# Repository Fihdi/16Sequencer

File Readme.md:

# 34hp 16 Step Sequencer

A 16-Step sequencer with individual CV knobs and 4 programmable gate outputs, including a probability gate output. Input gates can control the Clock, Reset, Direction and Pause/Play.

To program a gate channel, hold down the channel button (A through D) and select or deselect the steps are active. 

The functionality is similar to the famous "Baby 8" sequencers but instead of a CD4017, a TCA9555 IO-expander sends 5 or 0V to the potentiometers, which are then summed together. Another TCA9555 is used for the LEDs and push-buttons, both of which are set up in a 4x4 Matrix, allowing both of them to be handled by a single expander.

ToDo:

- Individual gate channel lengths: The length of every gate channel should be set individually with the LENGTH knob. Turning the LENGTH knob while holding down a channel button will change the length of that gate channel. Turning the LENGTH knob on its own only changes the length of the CV channel.

- Ratcheting: Pushing on a step button multiple times should allow for re-triggering (2, 4 or 8 times that of the CLK signal)

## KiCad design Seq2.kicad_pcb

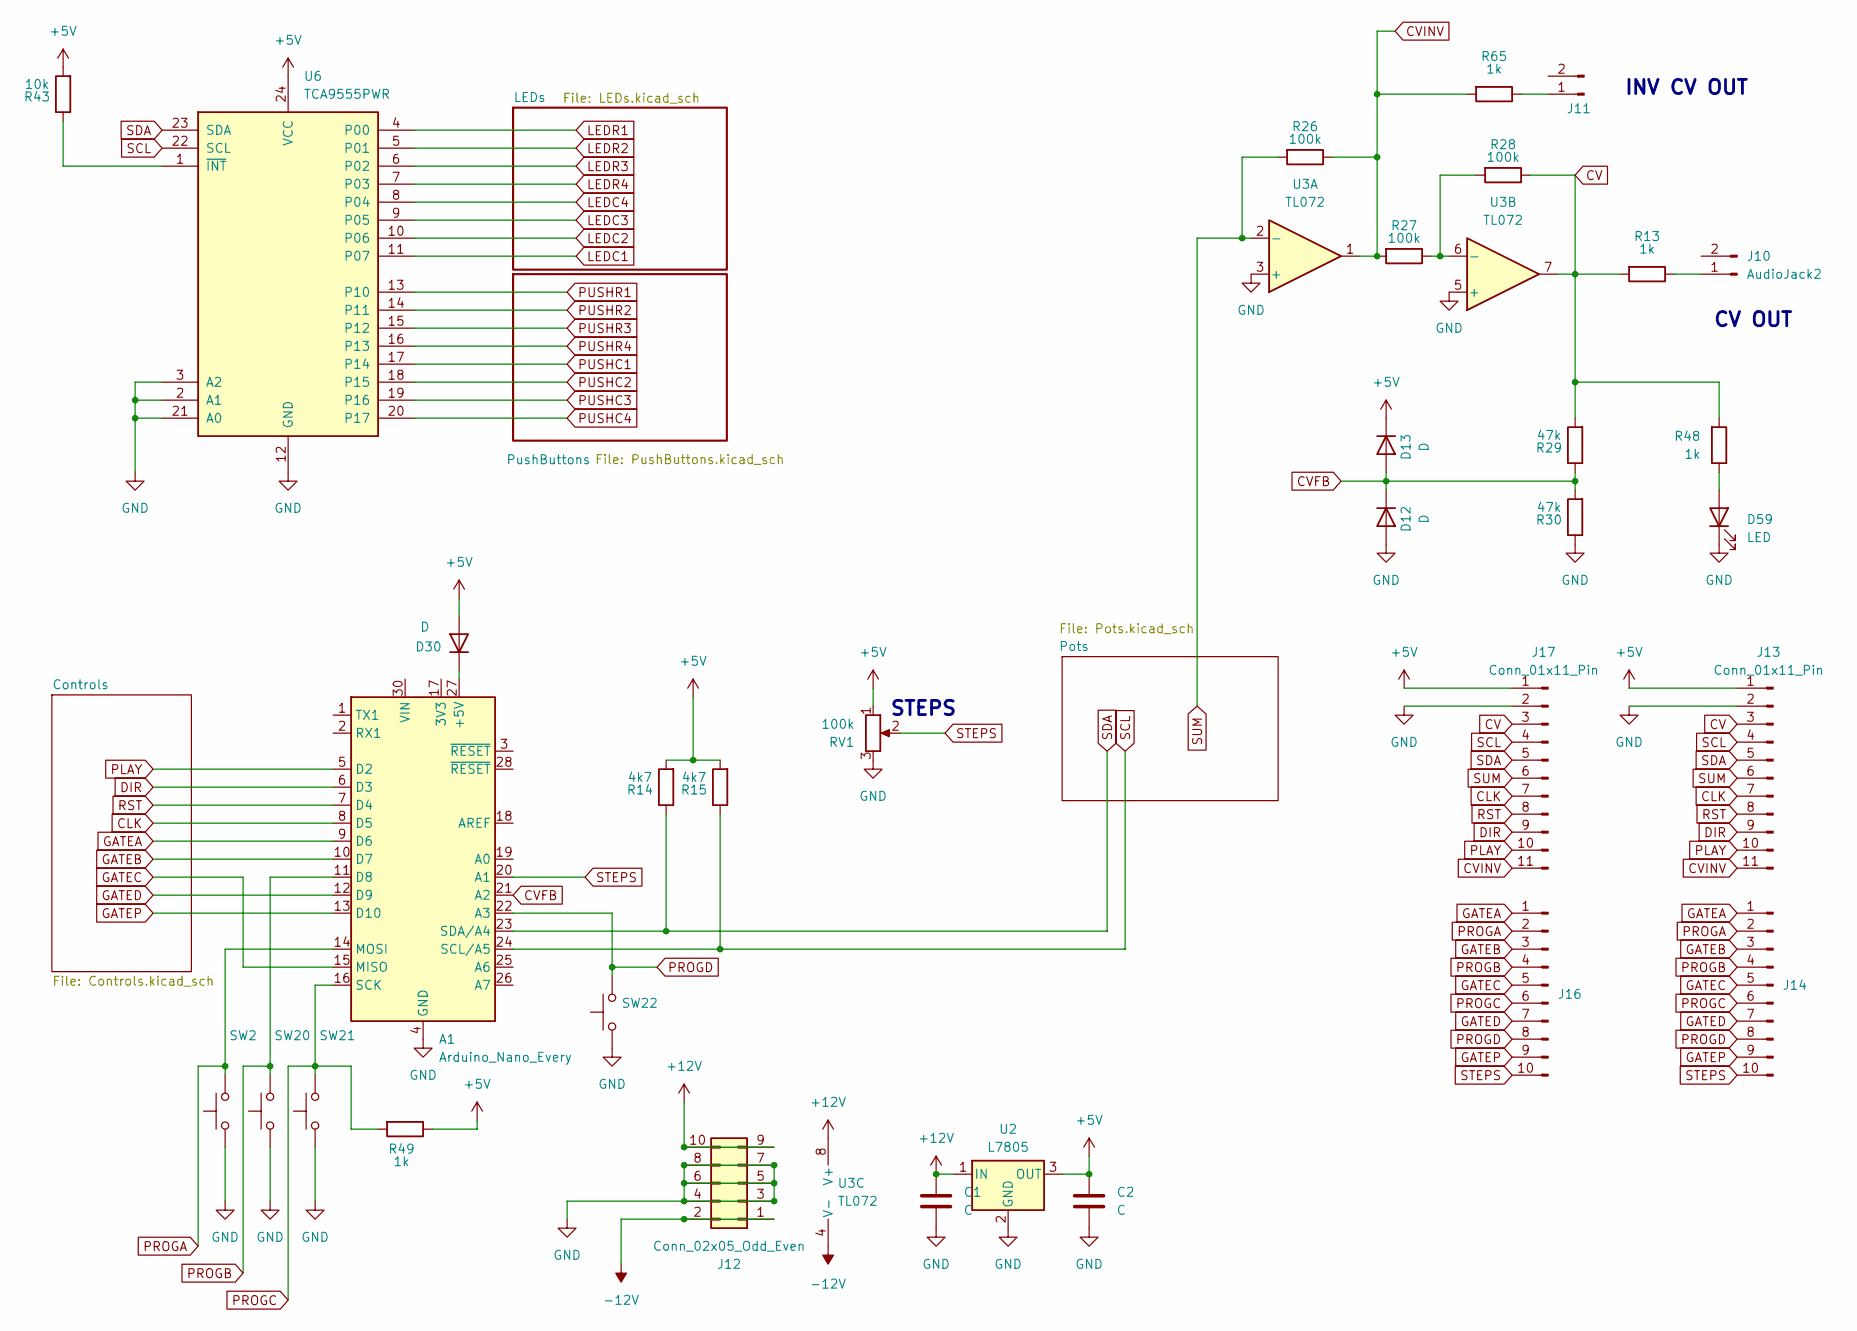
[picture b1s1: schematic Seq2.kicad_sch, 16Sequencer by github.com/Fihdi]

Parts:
A1: Arduino_Nano_Every; Arduino_Nano
C1, C2: C; C_Rect_L7.0mm_W3.5mm_P5.00mm
D12, D13, D30: D; D_1206_3216Metric
D59: LED; LED_D3.0mm
J10, J11: AudioJack2; 3mm5 Mono Aux
J12: Conn_02x05_Odd_Even; PinHeader_2x05_P2.54mm_Vertical
J13, J17: Conn_01x11_Pin; PinHeader_1x11_P2.54mm_Vertical
J14, J16: Conn_01x10_Pin; PinHeader_1x10_P2.54mm_Vertical
R13, R48, R49, R65: 1k; R_1206_3216Metric
R14, R15: 4k7; R_1206_3216Metric
R26, R27, R28: 100k; R_1206_3216Metric
R29, R30: 47k; R_1206_3216Metric
R43: 10k; R_1206_3216Metric
RV1: 100k; Potentiometer_Alpha_RD901F-40-00D_Single_Vertical_CircularH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
SW2, SW20, SW21, SW22: SW_Push; PushButton
U2: L7805; TO-252-3_TabPin2
U3: TL072; DIP-8_W7.62mm
U6: TCA9555PWR; SSOP-24_5.3x8.2mm_P0.65mm

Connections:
+5V: C2.1, D13.1 (K), D30.2 (A), J13.1, J17.1, R14.2, R15.2, R43.2, R49.1, RV1.1, U2.3 (OUT), U6.24 (VCC); also elsewhere on the board
+12V: C1.1, J12.9, J12.10, U2.1 (IN), U3.8 (V+)
-12V: J12.1, J12.2, U3.4 (V-)
CLK: A1.8 (D5), J13.7, J17.7; also elsewhere on the board
CV: J13.3, J17.3, R13.2, R28.1, R29.2, R48.2, U3.7
CVFB: A1.21 (A2), D12.1 (K), D13.2 (A), R29.1, R30.2
CVINV: J13.11, J17.11, R26.1, R27.2, R65.2, U3.1
DIR: A1.6 (D3), J13.9, J17.9; also elsewhere on the board
GATEA: A1.9 (D6), J14.1, J16.1; also elsewhere on the board
GATEB: A1.10 (D7), J14.3, J16.3; also elsewhere on the board
GATEC: A1.15 (MISO), J14.5, J16.5; also elsewhere on the board
GATED: A1.12 (D9), J14.7, J16.7; also elsewhere on the board
GATEP: A1.13 (D10), J14.9, J16.9; also elsewhere on the board
GND: A1.4 (GND), A1.29 (GND), C1.2, C2.2, D12.2 (A), D59.1 (K), J12.3, J12.4, J12.5, J12.6, J12.7, J12.8, J13.2, J17.2, R30.1, RV1.3, SW2.1, SW20.1, SW21.1, SW22.1, U2.2 (GND), U3.3 (+), U3.5 (+), U6.2 (A1), U6.3 (A2), U6.12 (GND), U6.21 (A0); also elsewhere on the board
LEDC1: U6.11 (P07); also elsewhere on the board
LEDC2: U6.10 (P06); also elsewhere on the board
LEDC3: U6.9 (P05); also elsewhere on the board
LEDC4: U6.8 (P04); also elsewhere on the board
LEDR1: U6.4 (P00); also elsewhere on the board
LEDR2: U6.5 (P01); also elsewhere on the board
LEDR3: U6.6 (P02); also elsewhere on the board
LEDR4: U6.7 (P03); also elsewhere on the board
unnamed: A1.27 (+5V), D30.1 (K)
unnamed: D59.2 (A), R48.1
unnamed: J10.1, R13.1
unnamed: J11.1, R65.1
unnamed: R27.1, R28.2, U3.6 (-)
unnamed: R43.1, U6.1 (~INT)
PLAY: A1.5 (D2), J13.10, J17.10; also elsewhere on the board
PROGA: A1.14 (MOSI), J14.2, J16.2, SW2.2
PROGB: A1.11 (D8), J14.4, J16.4, SW20.2
PROGC: A1.16 (SCK), J14.6, J16.6, R49.2, SW21.2
PROGD: A1.22 (A3), J14.8, J16.8, SW22.2
PUSHC1: U6.17 (P14); also elsewhere on the board
PUSHC2: U6.18 (P15); also elsewhere on the board
PUSHC3: U6.19 (P16); also elsewhere on the board
PUSHC4: U6.20 (P17); also elsewhere on the board
PUSHR1: U6.13 (P10); also elsewhere on the board
PUSHR2: U6.14 (P11); also elsewhere on the board
PUSHR3: U6.15 (P12); also elsewhere on the board
PUSHR4: U6.16 (P13); also elsewhere on the board
RST: A1.7 (D4), J13.8, J17.8; also elsewhere on the board
SCL: A1.24 (SCL/A5), J13.4, J17.4, R15.1, U6.22 (SCL); also elsewhere on the board
SDA: A1.23 (SDA/A4), J13.5, J17.5, R14.1, U6.23 (SDA); also elsewhere on the board
STEPS: A1.20 (A1), J14.10, J16.10, RV1.2
SUM: J13.6, J17.6, R26.2, U3.2 (-); also elsewhere on the board

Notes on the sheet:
STEPS
CV OUT
INV CV OUT

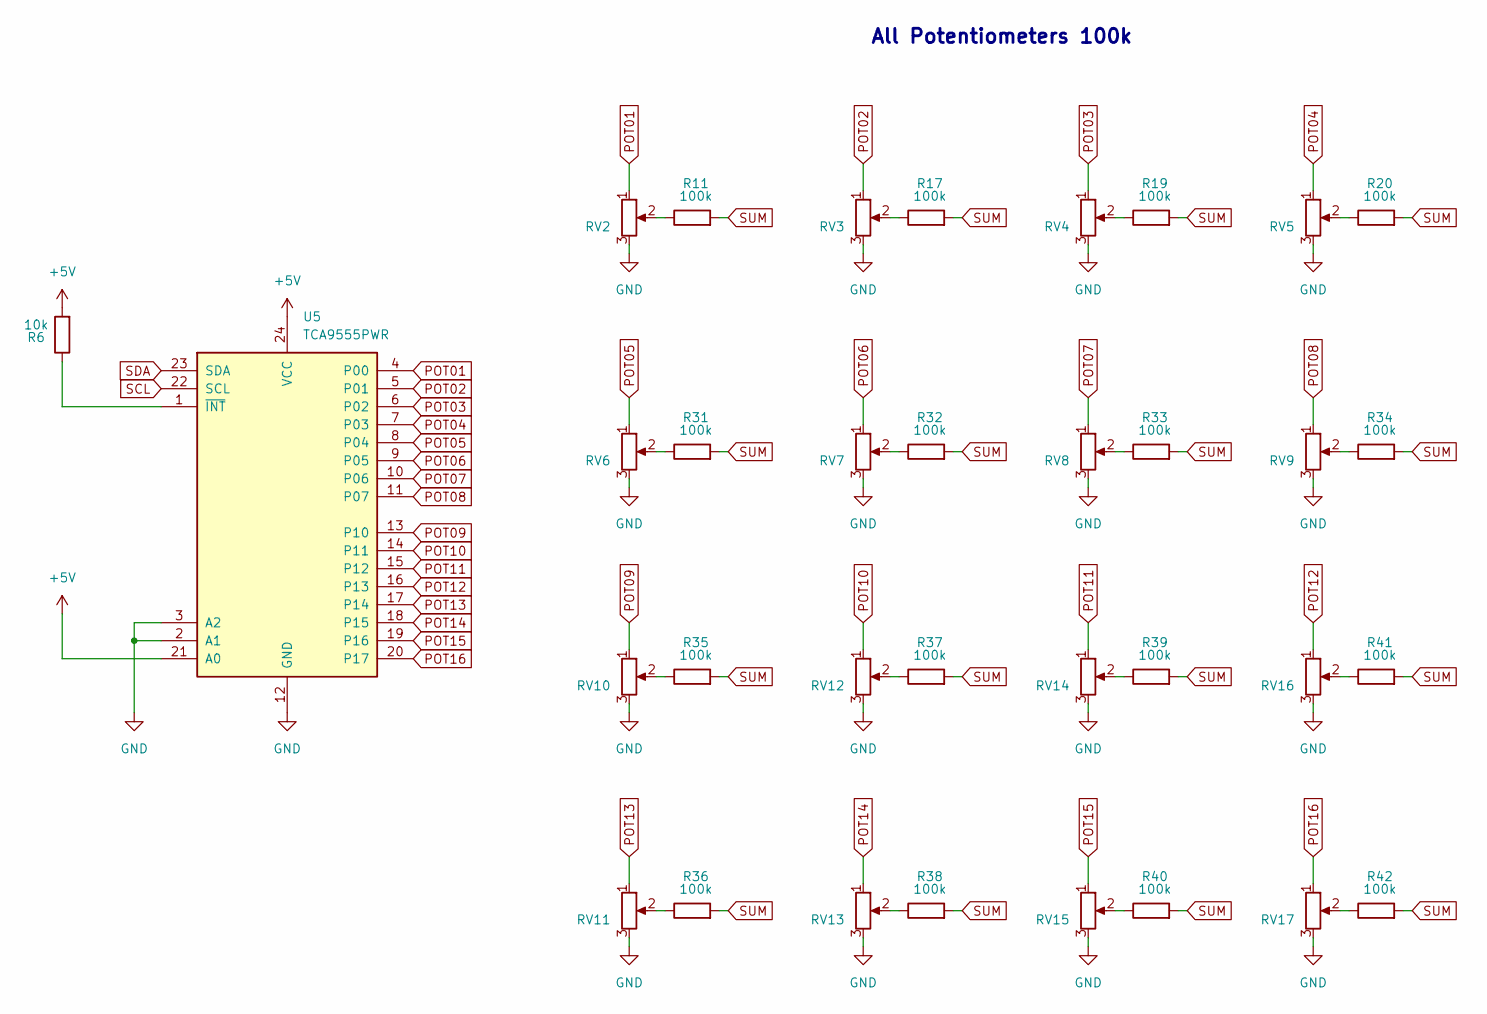
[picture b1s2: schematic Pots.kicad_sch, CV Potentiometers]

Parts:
R6: 10k; R_1206_3216Metric
R11, R17, R19, R20, R31, R32, R33, R34, R35, R36, R37, R38, R39, R40, R41, R42: 100k; R_1206_3216Metric
RV2, RV3, RV4, RV5, RV6, RV9, RV10, RV11, RV12, RV13, RV14, RV15, RV16, RV17: R_Potentiometer; Potentiometer_Alpha_RD901F-40-00D_Single_Vertical_CircularH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
RV7, RV8: R_Potentiometer; Alpha_RD901_NoMountPins
U5: TCA9555PWR; SSOP-24_5.3x8.2mm_P0.65mm

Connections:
+5V: R6.2, U5.21 (A0), U5.24 (VCC); also elsewhere on the board
GND: RV2.3, RV3.3, RV4.3, RV5.3, RV6.3, RV7.3, RV8.3, RV9.3, RV10.3, RV11.3, RV12.3, RV13.3, RV14.3, RV15.3, RV16.3, RV17.3, U5.2 (A1), U5.3 (A2), U5.12 (GND); also elsewhere on the board
unnamed: R11.1, RV2.2
unnamed: R17.1, RV3.2
unnamed: R19.1, RV4.2
unnamed: R20.1, RV5.2
unnamed: R31.1, RV6.2
unnamed: R32.1, RV7.2
unnamed: R33.1, RV8.2
unnamed: R34.1, RV9.2
unnamed: R35.1, RV10.2
unnamed: R36.1, RV11.2
unnamed: R37.1, RV12.2
unnamed: R38.1, RV13.2
unnamed: R39.1, RV14.2
unnamed: R40.1, RV15.2
unnamed: R41.1, RV16.2
unnamed: R42.1, RV17.2
unnamed: R6.1, U5.1 (~INT)
POT01: RV2.1, U5.4 (P00)
POT02: RV3.1, U5.5 (P01)
POT03: RV4.1, U5.6 (P02)
POT04: RV5.1, U5.7 (P03)
POT05: RV6.1, U5.8 (P04)
POT06: RV7.1, U5.9 (P05)
POT07: RV8.1, U5.10 (P06)
POT08: RV9.1, U5.11 (P07)
POT09: RV10.1, U5.13 (P10)
POT10: RV12.1, U5.14 (P11)
POT11: RV14.1, U5.15 (P12)
POT12: RV16.1, U5.16 (P13)
POT13: RV11.1, U5.17 (P14)
POT14: RV13.1, U5.18 (P15)
POT15: RV15.1, U5.19 (P16)
POT16: RV17.1, U5.20 (P17)
SCL: U5.22 (SCL); also elsewhere on the board
SDA: U5.23 (SDA); also elsewhere on the board
SUM: R11.2, R17.2, R19.2, R20.2, R31.2, R32.2, R33.2, R34.2, R35.2, R36.2, R37.2, R38.2, R39.2, R40.2, R41.2, R42.2; also elsewhere on the board

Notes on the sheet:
All Potentiometers 100k

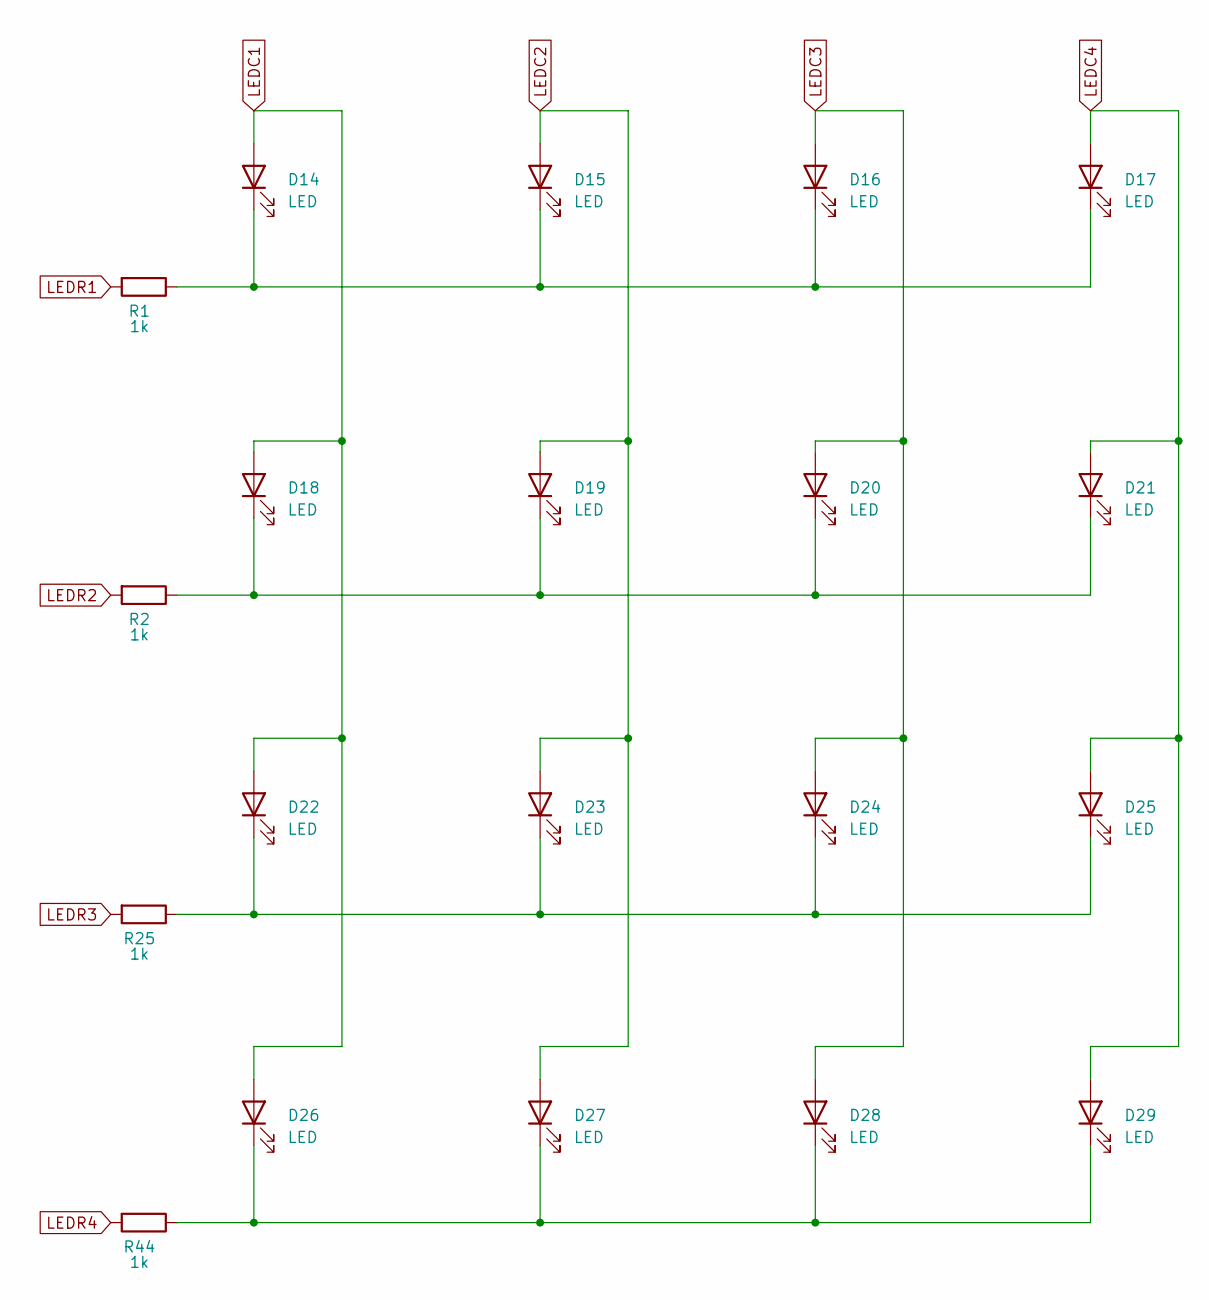
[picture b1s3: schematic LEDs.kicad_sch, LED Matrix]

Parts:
D14, D15, D16, D17, D18, D19, D20, D21, D22, D23, D24, D25, D26, D27, D28, D29: LED; LED_D3.0mm
R1, R2, R25, R44: 1k; R_1206_3216Metric

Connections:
LEDC1: D14.2 (A), D18.2 (A), D22.2 (A), D26.2 (A); also elsewhere on the board
LEDC2: D15.2 (A), D19.2 (A), D23.2 (A), D27.2 (A); also elsewhere on the board
LEDC3: D16.2 (A), D20.2 (A), D24.2 (A), D28.2 (A); also elsewhere on the board
LEDC4: D17.2 (A), D21.2 (A), D25.2 (A), D29.2 (A); also elsewhere on the board
LEDR1: R1.2; also elsewhere on the board
LEDR2: R2.2; also elsewhere on the board
LEDR3: R25.2; also elsewhere on the board
LEDR4: R44.2; also elsewhere on the board
unnamed: D14.1 (K), D15.1 (K), D16.1 (K), D17.1 (K), R1.1
unnamed: D18.1 (K), D19.1 (K), D20.1 (K), D21.1 (K), R2.1
unnamed: D22.1 (K), D23.1 (K), D24.1 (K), D25.1 (K), R25.1
unnamed: D26.1 (K), D27.1 (K), D28.1 (K), D29.1 (K), R44.1

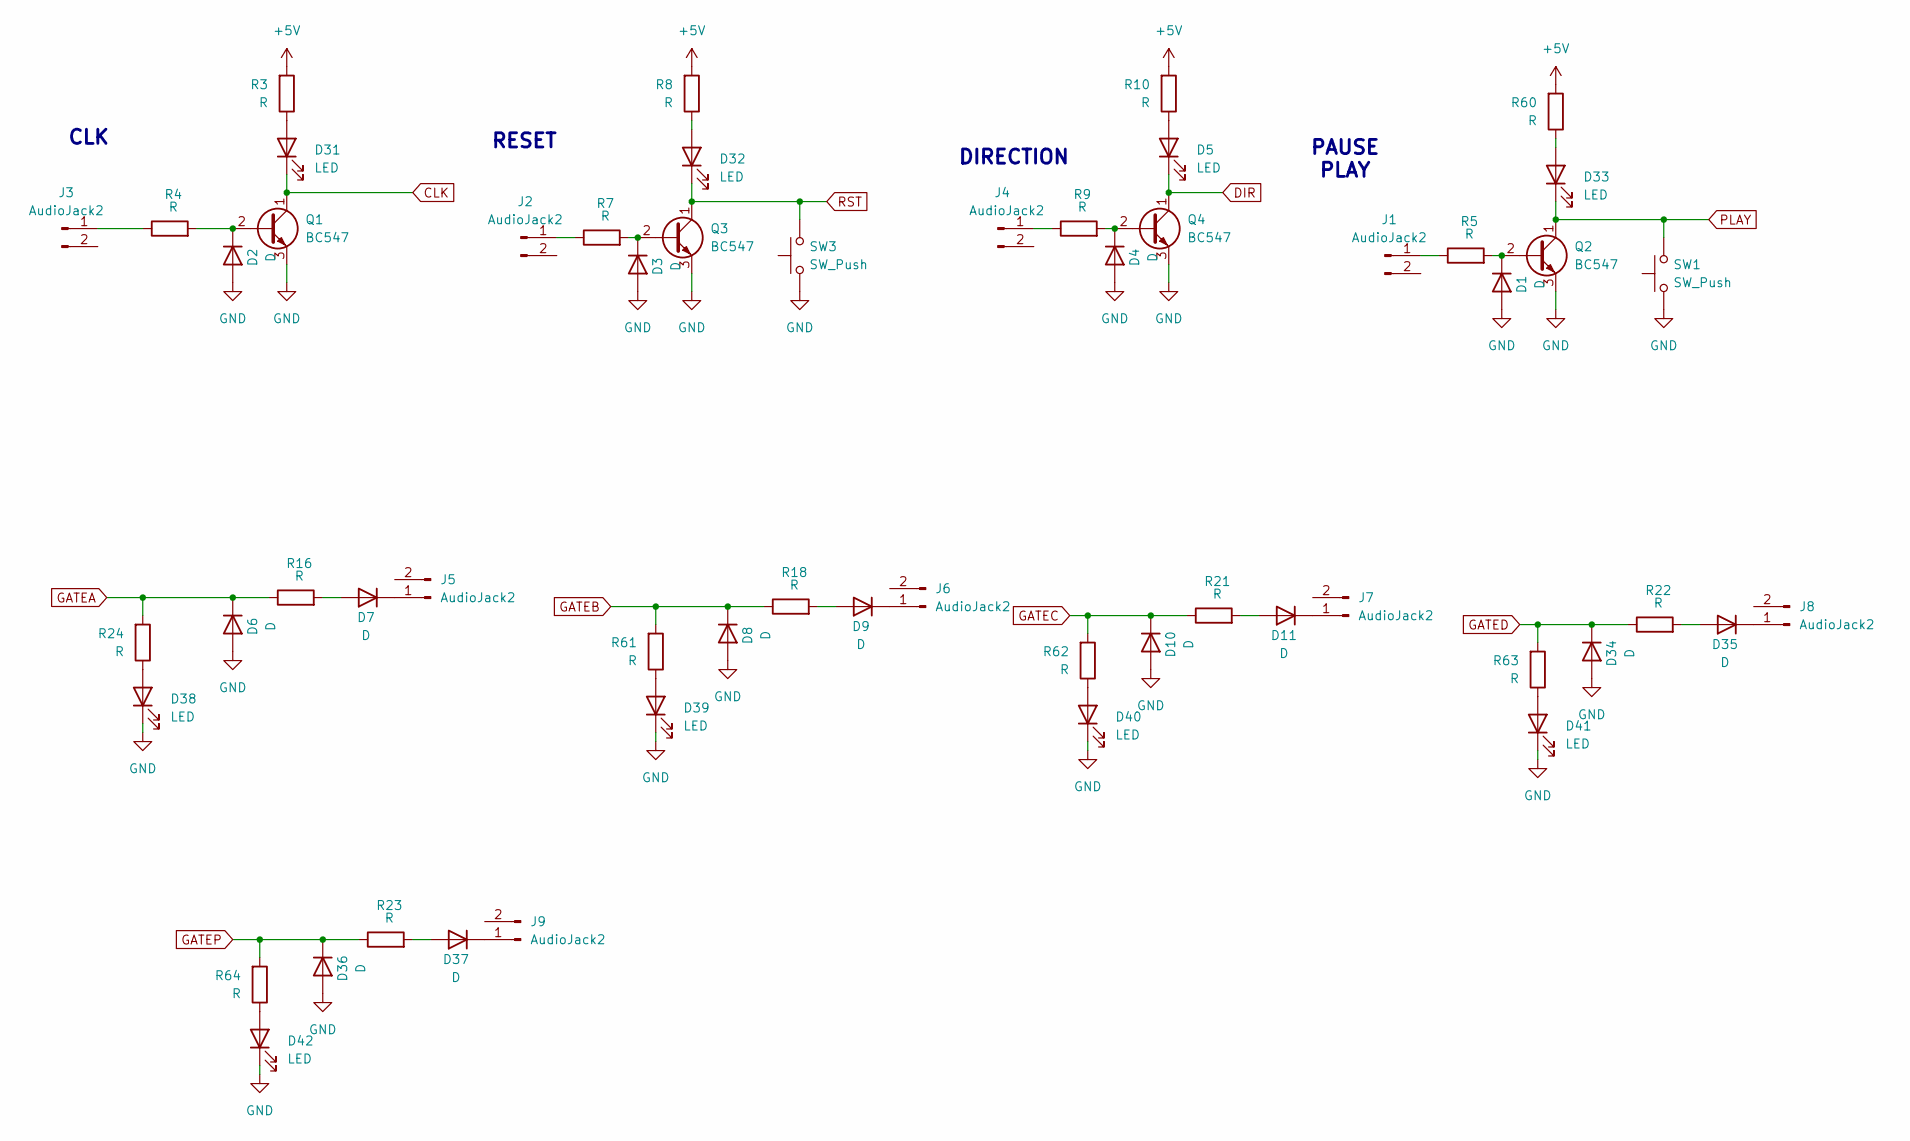
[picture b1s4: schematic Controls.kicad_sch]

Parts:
D1, D2, D3, D4, D6, D7, D8, D9, D10, D11, D34, D35, D36, D37: D; D_1206_3216Metric
D5, D31, D32, D33, D38, D39, D40, D41, D42: LED; LED_D3.0mm
J1, J2, J3, J4, J5, J6, J7, J8, J9: AudioJack2; 3mm5 Mono Aux
Q1, Q2, Q3, Q4: BC547; TO-92L_Inline_Wide
R3, R4, R5, R7, R8, R9, R10, R16, R18, R21, R22, R23, R24, R60, R61, R62, R63, R64: R; R_1206_3216Metric
SW1, SW3: SW_Push; PushButton

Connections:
+5V: R3.2, R8.2, R10.2, R60.2; also elsewhere on the board
CLK: D31.1 (K), Q1.1 (C); also elsewhere on the board
DIR: D5.1 (K), Q4.1 (C); also elsewhere on the board
GATEA: D6.1 (K), R16.1, R24.2; also elsewhere on the board
GATEB: D8.1 (K), R18.1, R61.2; also elsewhere on the board
GATEC: D10.1 (K), R21.1, R62.2; also elsewhere on the board
GATED: D34.1 (K), R22.1, R63.2; also elsewhere on the board
GATEP: D36.1 (K), R23.1, R64.2; also elsewhere on the board
GND: D1.2 (A), D2.2 (A), D3.2 (A), D4.2 (A), D6.2 (A), D8.2 (A), D10.2 (A), D34.2 (A), D36.2 (A), D38.1 (K), D39.1 (K), D40.1 (K), D41.1 (K), D42.1 (K), Q1.3 (E), Q2.3 (E), Q3.3 (E), Q4.3 (E), SW1.1, SW3.1; also elsewhere on the board
unnamed: D1.1 (K), Q2.2 (B), R5.2
unnamed: D2.1 (K), Q1.2 (B), R4.2
unnamed: D3.1 (K), Q3.2 (B), R7.2
unnamed: D4.1 (K), Q4.2 (B), R9.2
unnamed: D5.2 (A), R10.1
unnamed: D7.2 (A), R16.2
unnamed: D7.1 (K), J5.1
unnamed: D9.2 (A), R18.2
unnamed: D9.1 (K), J6.1
unnamed: D11.2 (A), R21.2
unnamed: D11.1 (K), J7.1
unnamed: D31.2 (A), R3.1
unnamed: D32.2 (A), R8.1
unnamed: D33.2 (A), R60.1
unnamed: D35.2 (A), R22.2
unnamed: D35.1 (K), J8.1
unnamed: D37.2 (A), R23.2
unnamed: D37.1 (K), J9.1
unnamed: D38.2 (A), R24.1
unnamed: D39.2 (A), R61.1
unnamed: D40.2 (A), R62.1
unnamed: D41.2 (A), R63.1
unnamed: D42.2 (A), R64.1
unnamed: J1.1, R5.1
unnamed: J2.1, R7.1
unnamed: J3.1, R4.1
unnamed: J4.1, R9.1
PLAY: D33.1 (K), Q2.1 (C), SW1.2; also elsewhere on the board
RST: D32.1 (K), Q3.1 (C), SW3.2; also elsewhere on the board

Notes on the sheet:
DIRECTION
CLK
PAUSE PLAY
RESET

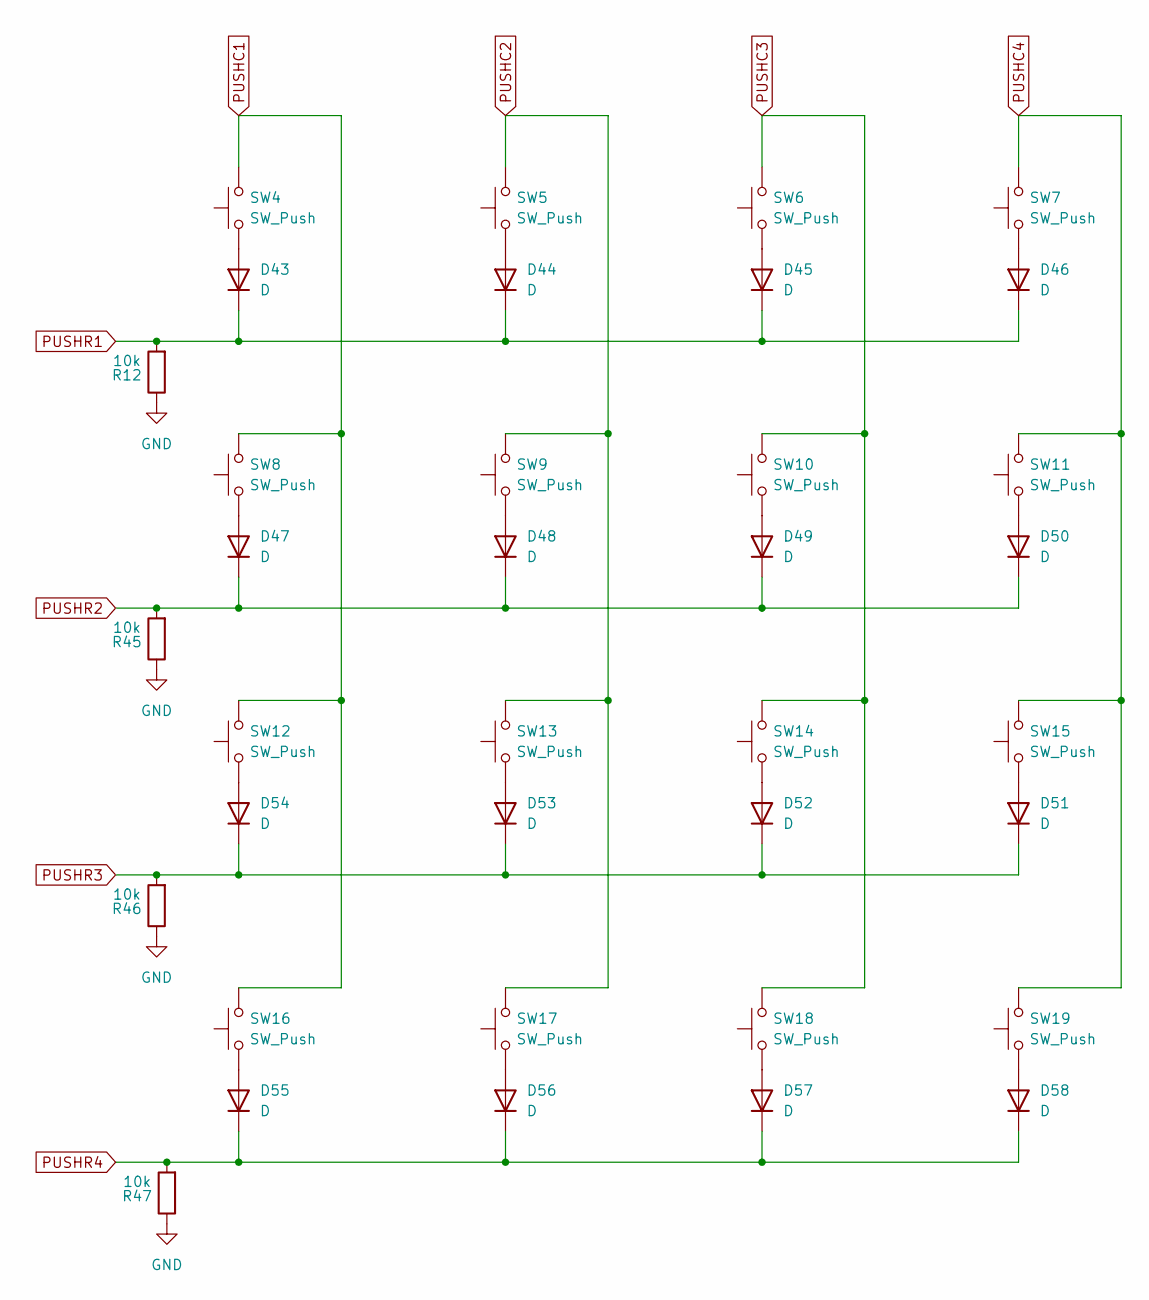
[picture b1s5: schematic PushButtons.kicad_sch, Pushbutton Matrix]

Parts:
D43, D44, D45, D46, D47, D48, D49, D50, D51, D52, D53, D54, D55, D56, D57, D58: D; D_1206_3216Metric
R12, R45, R46, R47: 10k; R_1206_3216Metric
SW4, SW5, SW6, SW7, SW8, SW9, SW10, SW11, SW12, SW13, SW14, SW15, SW16, SW17, SW18, SW19: SW_Push; PushButton

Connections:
GND: R12.1, R45.1, R46.1, R47.1; also elsewhere on the board
unnamed: D43.2 (A), SW4.1
unnamed: D44.2 (A), SW5.1
unnamed: D45.2 (A), SW6.1
unnamed: D46.2 (A), SW7.1
unnamed: D47.2 (A), SW8.1
unnamed: D48.2 (A), SW9.1
unnamed: D49.2 (A), SW10.1
unnamed: D50.2 (A), SW11.1
unnamed: D51.2 (A), SW15.1
unnamed: D52.2 (A), SW14.1
unnamed: D53.2 (A), SW13.1
unnamed: D54.2 (A), SW12.1
unnamed: D55.2 (A), SW16.1
unnamed: D56.2 (A), SW17.1
unnamed: D57.2 (A), SW18.1
unnamed: D58.2 (A), SW19.1
PUSHC1: SW4.2, SW8.2, SW12.2, SW16.2; also elsewhere on the board
PUSHC2: SW5.2, SW9.2, SW13.2, SW17.2; also elsewhere on the board
PUSHC3: SW6.2, SW10.2, SW14.2, SW18.2; also elsewhere on the board
PUSHC4: SW7.2, SW11.2, SW15.2, SW19.2; also elsewhere on the board
PUSHR1: D43.1 (K), D44.1 (K), D45.1 (K), D46.1 (K), R12.2; also elsewhere on the board
PUSHR2: D47.1 (K), D48.1 (K), D49.1 (K), D50.1 (K), R45.2; also elsewhere on the board
PUSHR3: D51.1 (K), D52.1 (K), D53.1 (K), D54.1 (K), R46.2; also elsewhere on the board
PUSHR4: D55.1 (K), D56.1 (K), D57.1 (K), D58.1 (K), R47.2; also elsewhere on the board

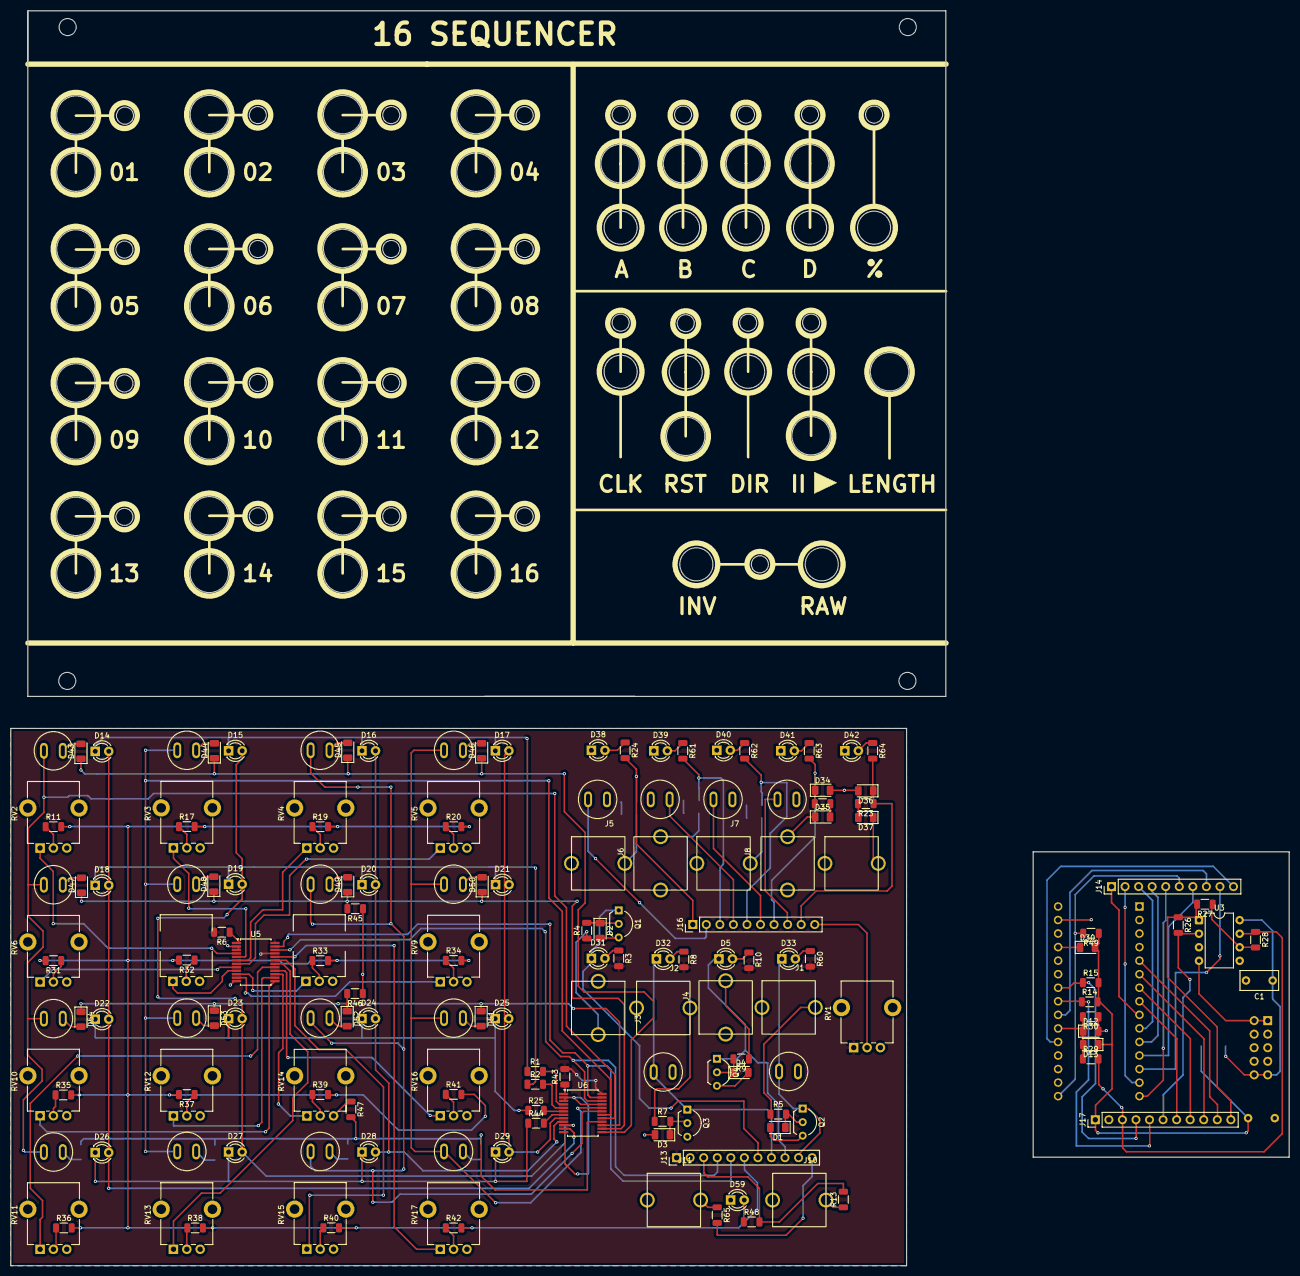
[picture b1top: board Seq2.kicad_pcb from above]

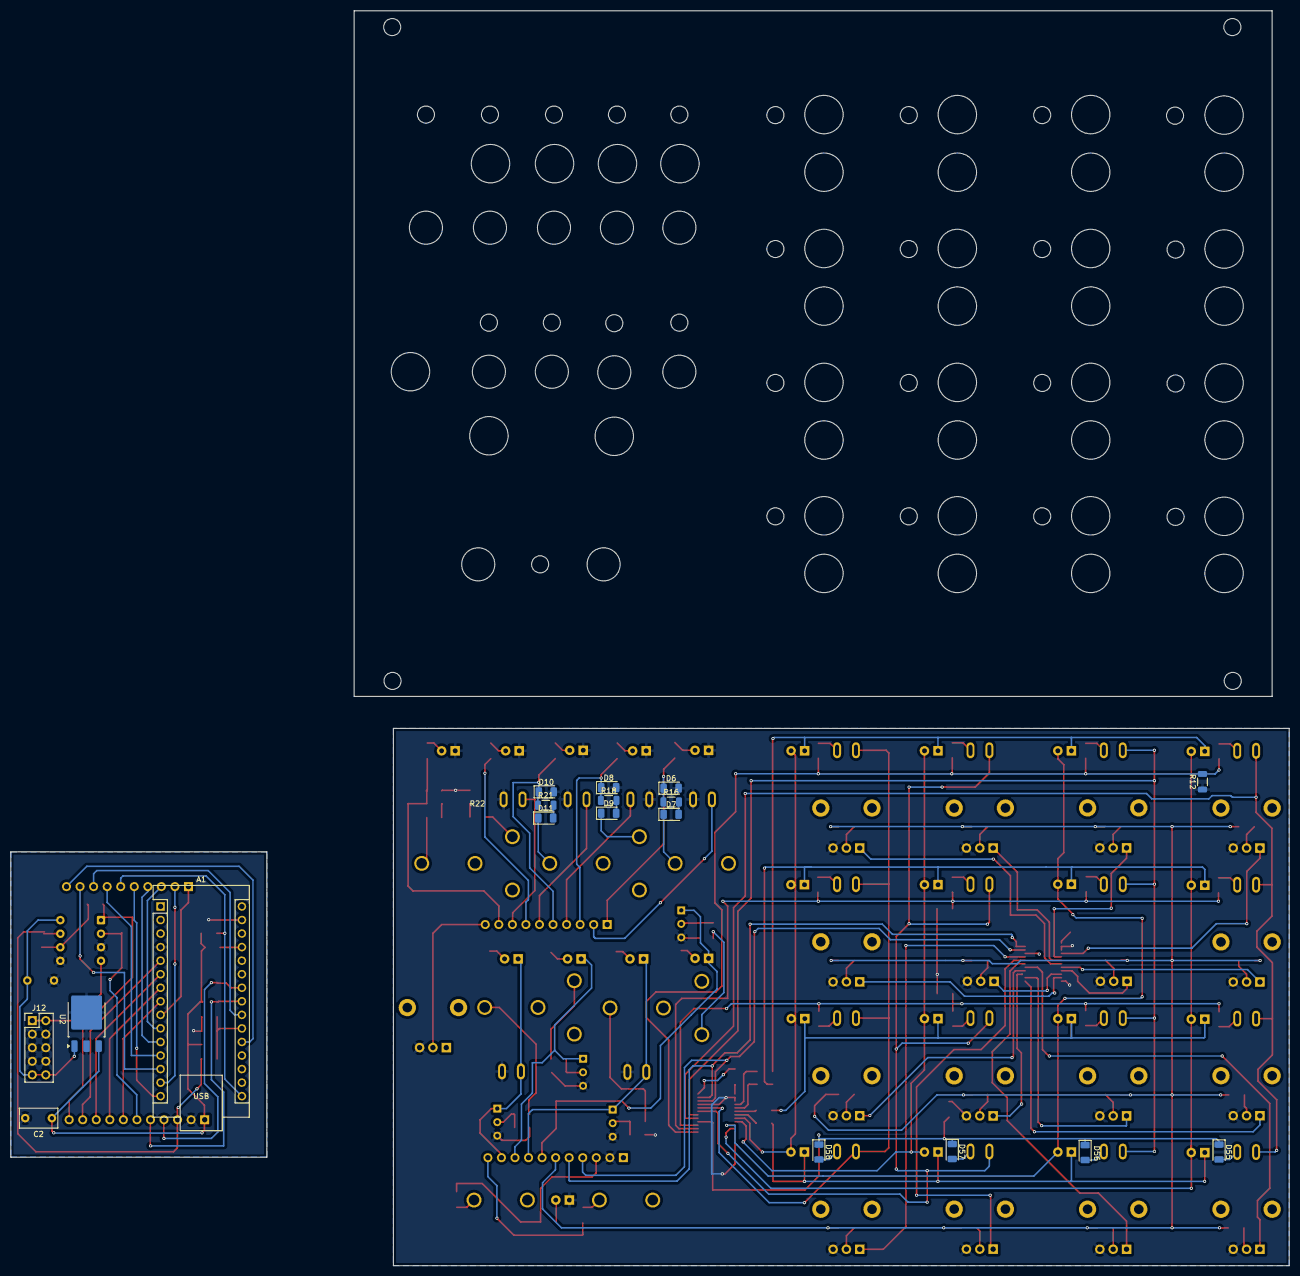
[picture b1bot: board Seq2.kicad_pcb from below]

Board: 2 copper layers, 167.9 x 100.7 mm, 180 parts (18 on the bottom side), 126 nets.

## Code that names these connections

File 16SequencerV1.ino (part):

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
//Arduino Nano Pins

#define PLAY 2     //Pause and Play input
#define DIR 3      //Direction input
#define RST 4      //Reset input
#define CLK 5      //Clock input
#define LENGTH A1  //Length Input
#define CVFB A2

#define PROGA 11  //Button Input for programming the A-Gates
#define PROGB 8   //Button Input for programming the B-Gates
#define PROGC 13  //Button Input for programming the C-Gates
#define PROGD A3  //Button Input for programming the D-Gates

#define GATEA 6   //GATE A output
#define GATEB 7   //GATE B output
#define GATEC 12  //GATE C output
#define GATED 9   //GATE D output
#define GATEP 10  //Probability Gate Output

//LED and Pushbutton IO Expander Pins

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int lastCV = 0;        // last value from the length potentiometer
long timemarkLength = 0;   //timemark until the length should stay displayed

long timemarkCVFB = 0;    // timemark to read in CVFB after Clock signal
bool CVFBread = false;    // boolean if the CVFB has been read in yet after a CLK

int LEDMatrixCounter = 0;  // Counter to display the LEDs
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  LEDPUSHEXPANDER.pinMode1(PUSHROW3, INPUT);
  LEDPUSHEXPANDER.pinMode1(PUSHROW4, INPUT);

  pinMode(PROGA, INPUT_PULLUP);
  pinMode(PROGB, INPUT_PULLUP);
  pinMode(PROGC, INPUT_PULLUP);
  pinMode(PROGD, INPUT_PULLUP);

  pinMode(GATEA, OUTPUT);
  pinMode(GATEB, OUTPUT);
  pinMode(GATEC, OUTPUT);
  pinMode(GATED, OUTPUT);
  pinMode(GATEP, OUTPUT);

  pinMode(CLK, INPUT_PULLUP);
  pinMode(RST, INPUT_PULLUP);
  pinMode(DIR, INPUT_PULLUP);
  pinMode(PLAY, INPUT_PULLUP);
  pinMode(LENGTH, INPUT);

  LEDPUSHEXPANDER.write1(LEDROW1, HIGH);
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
